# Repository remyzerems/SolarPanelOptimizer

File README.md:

# Solar Panel Optimizer
A project to get the most out of your solar panel of your house by intelligently controlling your boiler !

### Project context
The goal of an (electric) boiler is to transform electrical power into heat to make some hot water inside a tank.
If your home has no specific installation, the boiler switches on as soon as the water inside the tank falls down to a given temperature threshold.
If your home has a specific installation (i.e. day/night rates) this only occurs at night when the rates are lower.

Now if you have solar panels, the energy they are producing from the sun is either injected into your house to power some of your devices (oven, computer...) or either injected to the mains network (i.e. outside of your house, to your neighbourhood).
In the latter case, your electric provider will pay you a fraction (I mean less than one uh !) of what you pay for each kWh you consume.

As a result each solar panel produced kWh that does not power something in your house is not efficently used...

There comes our project !

### Project goal
The idea of the project is mainly inspired from [Barnabé Chaillot project](https://github.com/sgalvagno/Chaillot_Barnabe_Autoconsommation_photovoltaique).
He described a way to control the power that is sent to his boiler based on the power produced by the solar panels.
To be more precise, it is based on the available power at the house level.
Indeed the house electrical devices are consuming a given amount of energy that may or may not be absorbing all what the solar panels are producing.

The goal of the system is to only power the boiler on the exceeding power from the house.
The system has to carefully control the boiler power to make the house power balance null.
This way the energy produced by our solar panels is optimally used and than we only sell the exceeding energy that we do not need.

So we've been inspired by Barnabé project and decided to push it a little bit further and to have fun developping it.

### System features
The system we developped has the following features :
* Control of the electrical power injected to the boiler based on available solar panel excess power
* Measurement of the following currents:
  * House global
  * Solar panel production
  * Boiler consumption
* Hot water guard (switching the boiler ON at night if the solar panel production had not been sufficient to heat the water)
* Dedicated PCB board with some extension capacities (see board features for details)

### PCB board features

* Arduino Nano based
* Clean and user friendly design
* Inputs
  * 3x current probes
  * 1x mains signal image
  * 4x digital IOs (e.g. push button inputs)
* Outputs
  * Galvanicaly isolated variable resistor (i.e. to control a SCR that powers the boiler)
  * 3x transistor controllable loads, 0-24V, 5A (e.g. relays)
* Communication busses
  * 3x I2C connectors (LCD display, RTC and a spare connector)
* Power inputs
  * Arduino power through USB connector
  * External power input to power stuff (relays mainly)

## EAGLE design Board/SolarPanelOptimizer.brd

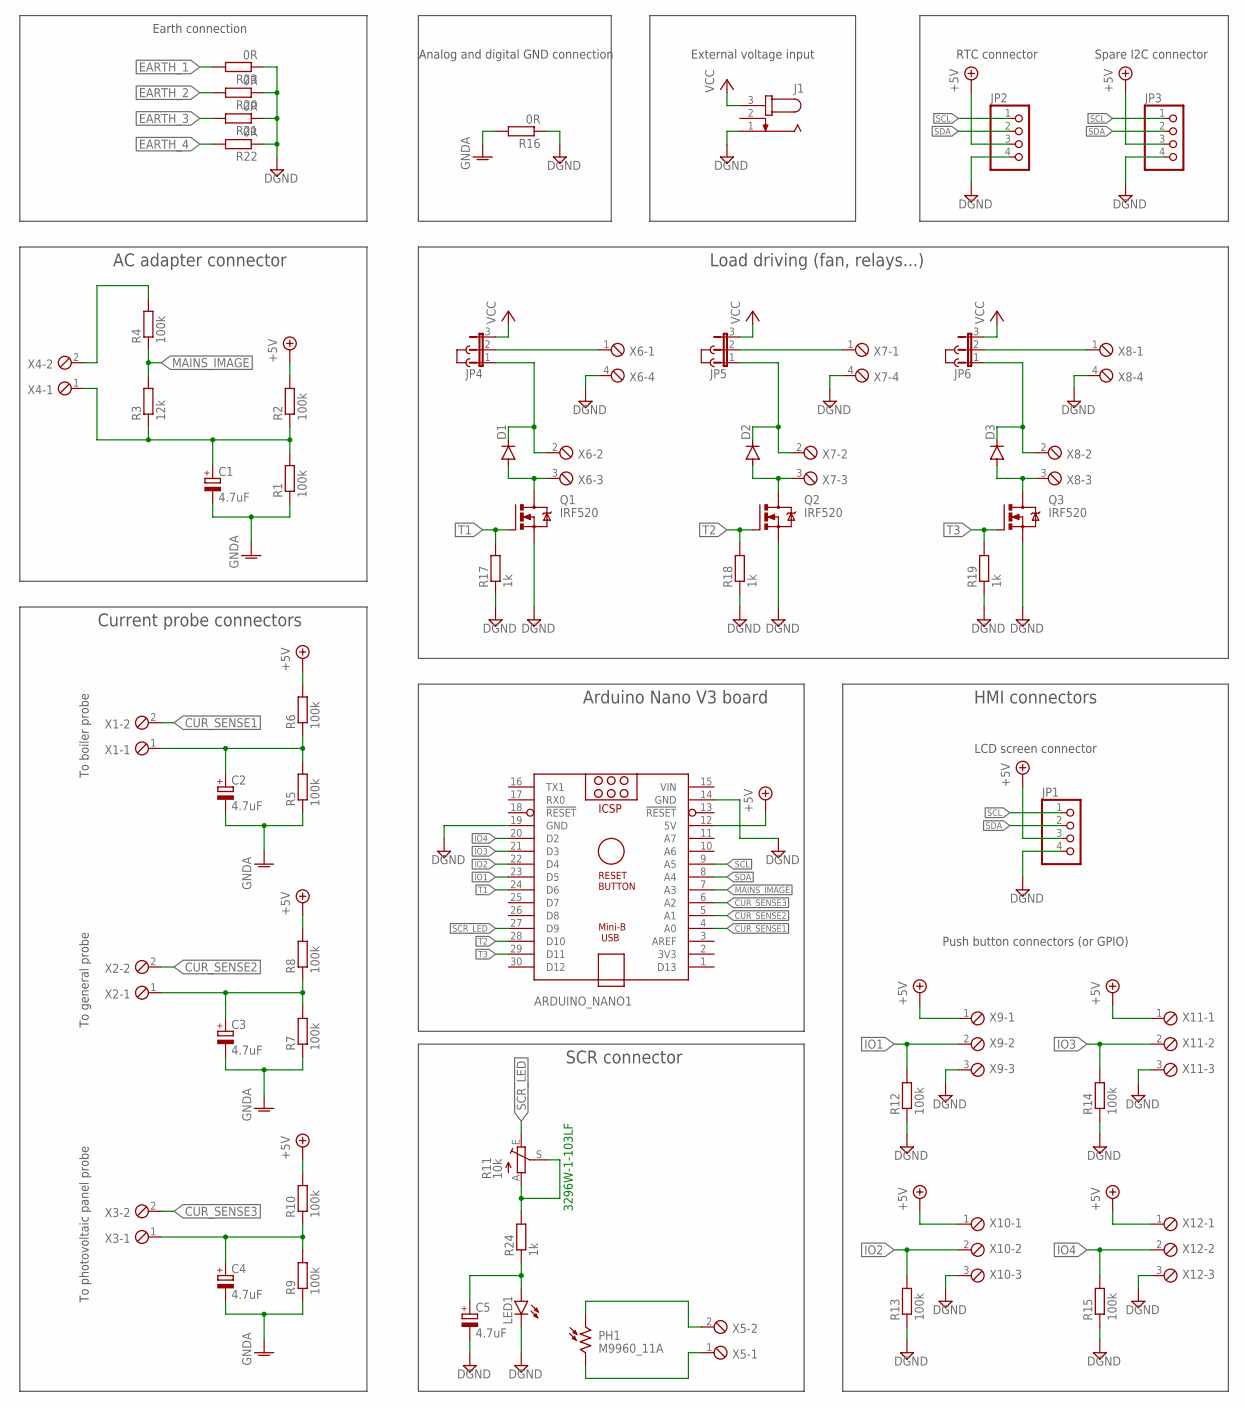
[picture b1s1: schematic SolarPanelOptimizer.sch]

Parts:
ARDUINO_NANO1: ARDUINO_NANO
C1, C2, C3, C4, C5: 4.7uF; E2-5
D1, D2, D3: DIODE-D-2.5; D-2.5
J1: JACK-PLUG0; SPC4077
J2, J3, J4: JUMPER; JUMP
JP1, JP2, JP3: PINHD-1X4; 1X04
JP4, JP5, JP6: JP2E; JP2
LED1: LED3MM
PH1: M9960_11A; M9960
Q1, Q2, Q3: IRF520; TO220BV
R1, R2, R4, R5, R6, R7, R8, R9, R10, R12, R13, R14, R15: 100k; 0204V
R3: 12k; 0204V
R11: 10k; RJ9W
R16, R20, R21, R22, R23: 0R; R0805
R17, R18, R19, R24: 1k; 0204V
X1, X2, X3, X4, X5: MPT2-REAL; 2POL254-REAL
X6, X7, X8: MPT4-REAL; 4POL254-REAL
X9, X10, X11, X12: MPT3-REAL; 3POL254-REAL

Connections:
CUR_SENSE1: ARDUINO_NANO1.4 (A0), X1.2
CUR_SENSE2: ARDUINO_NANO1.5 (A1), X2.2
CUR_SENSE3: ARDUINO_NANO1.6 (A2), X3.2
DGND: ARDUINO_NANO1.14 (GND), ARDUINO_NANO1.19 (GND), C5.-, J1.1, JP1.4, JP2.4, JP3.4, LED1.K (C), Q1.S, Q2.S, Q3.S, R12.1, R13.1, R14.1, R15.1, R16.1, R17.1, R18.1, R19.1, R20.1, R21.1, R22.1, R23.1, X6.4, X7.4, X8.4, X9.3, X10.3, X11.3, X12.3
EARTH_1: R23.2
EARTH_2: R20.2
EARTH_3: R21.2
EARTH_4: R22.2
GNDA: C1.-, C2.-, C3.-, C4.-, R1.1, R5.1, R7.1, R9.1, R16.2
IO1: ARDUINO_NANO1.23 (D5), R12.2, X9.2
IO2: ARDUINO_NANO1.22 (D4), R13.2, X10.2
IO3: ARDUINO_NANO1.21 (D3), R14.2, X11.2
IO4: ARDUINO_NANO1.20 (D2), R15.2, X12.2
MAINS_IMAGE: ARDUINO_NANO1.7 (A3), R3.2, R4.1
unnamed: C1.+, R1.2, R2.1, R3.1, X4.1
unnamed: C2.+, R5.2, R6.1, X1.1
unnamed: C3.+, R7.2, R8.1, X2.1
unnamed: C4.+, R9.2, R10.1, X3.1
unnamed: R4.2, X4.2
unnamed: PH1.1, X5.2
unnamed: C5.+, LED1.A, R24.1
unnamed: PH1.2, X5.1
unnamed: D2.A, Q2.D, X7.3
unnamed: R11.A, R11.S, R24.2
unnamed: JP4.2, X6.1
unnamed: D1.A, Q1.D, X6.3
unnamed: D1.C, JP4.1, X6.2
unnamed: D2.C, JP5.1, X7.2
unnamed: JP5.2, X7.1
unnamed: D3.A, Q3.D, X8.3
unnamed: D3.C, JP6.1, X8.2
unnamed: JP6.2, X8.1
SCL: ARDUINO_NANO1.9 (A5), JP1.1, JP2.1, JP3.1
SCR_LED: ARDUINO_NANO1.27 (D9), R11.E
SDA: ARDUINO_NANO1.8 (A4), JP1.2, JP2.2, JP3.2
T1: ARDUINO_NANO1.24 (D6), Q1.G, R17.2
T2: ARDUINO_NANO1.28 (D10), Q2.G, R18.2
T3: ARDUINO_NANO1.29 (D11), Q3.G, R19.2
VCC: J1.3, JP4.3, JP5.3, JP6.3
VDD: ARDUINO_NANO1.12 (5V), JP1.3, JP2.3, JP3.3, R2.2, R6.2, R8.2, R10.2, X9.1, X10.1, X11.1, X12.1
VIN: ARDUINO_NANO1.15 (VIN)

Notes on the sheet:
AC adapter connector
3296W-1-103LF
LCD screen connector
Current probe connectors
HMI connectors
Push button connectors (or GPIO)
SCR connector
To boiler probe
To general probe
To photovoltaic panel probe
Arduino Nano V3 board
RTC connector
Load driving (fan, relays...)
Spare I2C connector
External voltage input
Earth connection
Analog and digital GND connection

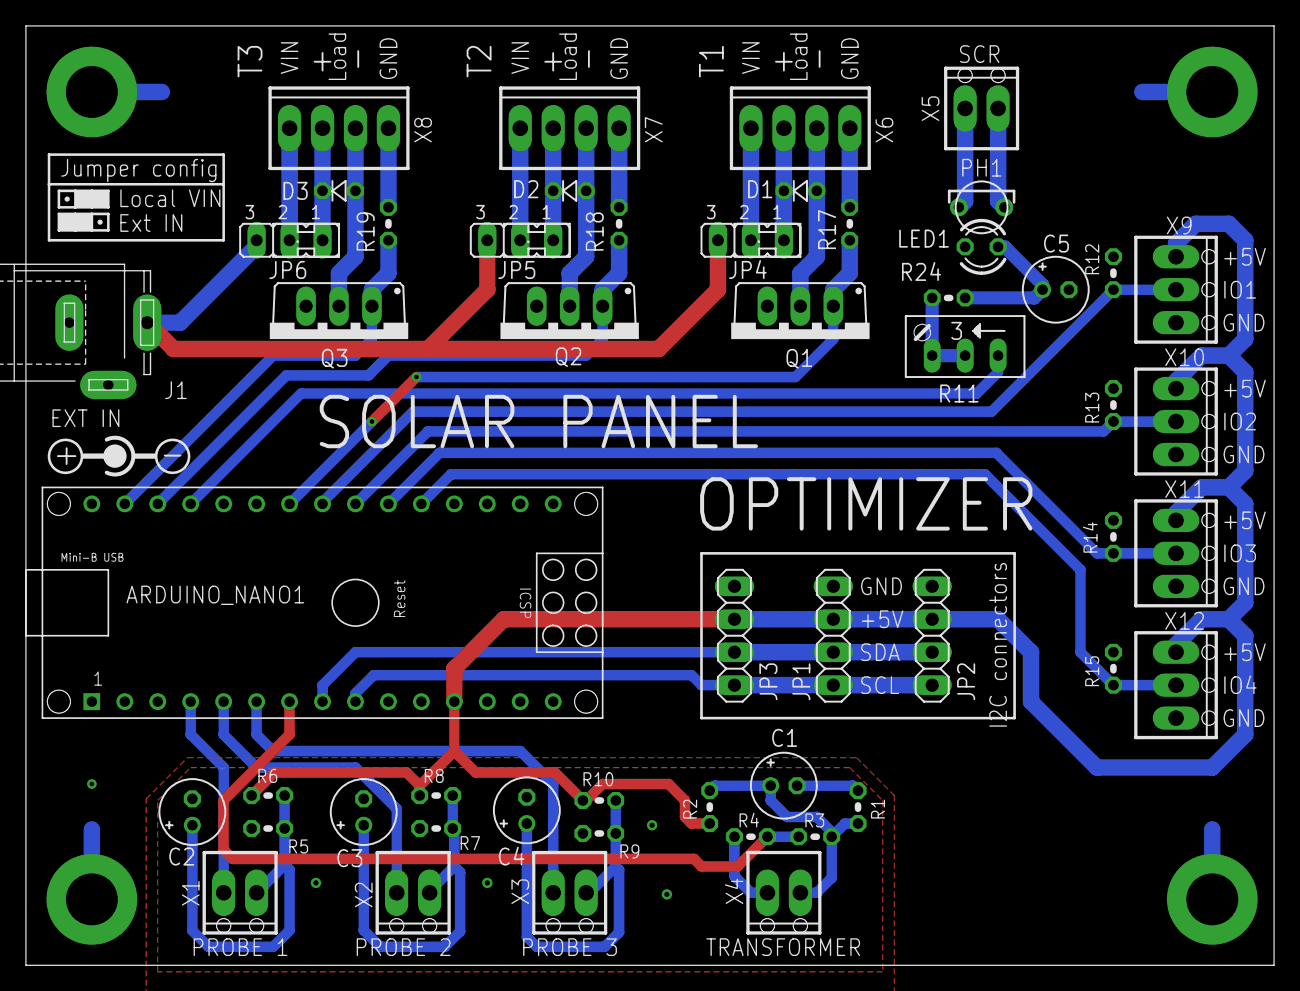
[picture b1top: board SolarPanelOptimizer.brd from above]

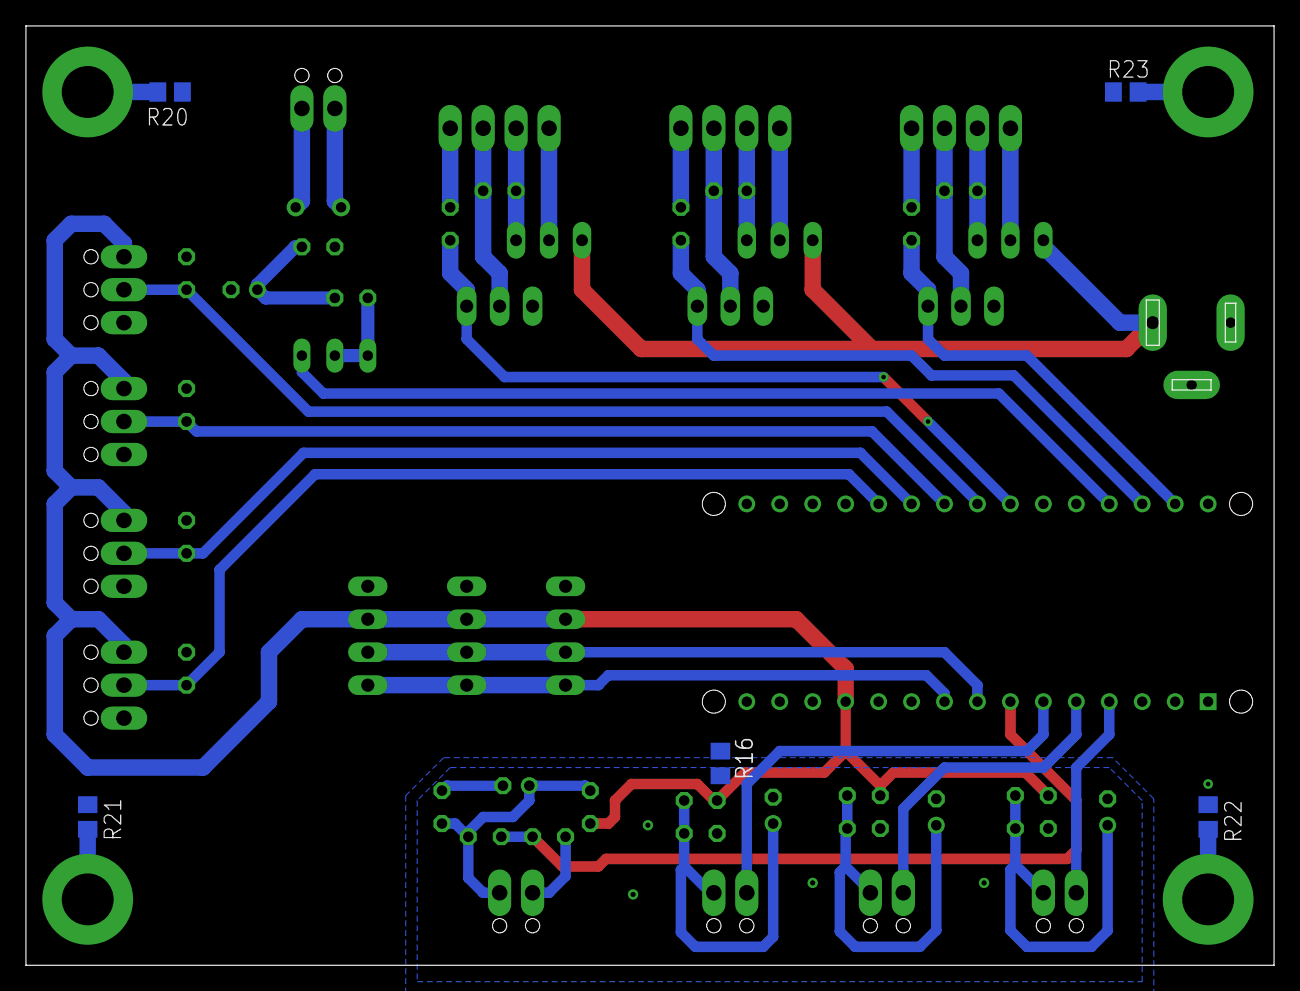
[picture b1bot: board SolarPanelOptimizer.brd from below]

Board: 2 copper layers, 96.2 x 72.4 mm, 60 parts (5 on the bottom side), 36 nets.

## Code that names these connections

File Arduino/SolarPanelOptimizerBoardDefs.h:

#ifndef __SOLAR_PANEL_OPTIMIZER_BOARD__
#define __SOLAR_PANEL_OPTIMIZER_BOARD__

// Digital IO
#define IO1			5
#define IO2			4
#define IO3			3
#define IO4			2

// PWMs
#define SCR_LED		9
#define T1			5
#define T2			10
#define T3			11

#define MAX_PWM_16_BITS		(65535L)
#define MAX_PWM_8_BITS		(255L)

// Current probes
#define CUR_SENSE1			0
#define CUR_SENSE2			1
#define CUR_SENSE3			2
#define CUR_SENSE_COUNT		3

// Mains voltage image
#define MAINS_IMAGE			3


// Functions

void board_setup(void);

long int getPWMMaxDuty(int pin);
void setPWM(int pin, unsigned int duty);
void setPWM(int pin, long int duty);
void setPWM(int pin, float duty);

#endif

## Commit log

2021-11-04 Initial delivery
2021-12-27 Changed night mode to forced heat. User can force heating. Bug fix.
    Trying to fix when the boiler not heating at night when it did not heat enough during the day.
